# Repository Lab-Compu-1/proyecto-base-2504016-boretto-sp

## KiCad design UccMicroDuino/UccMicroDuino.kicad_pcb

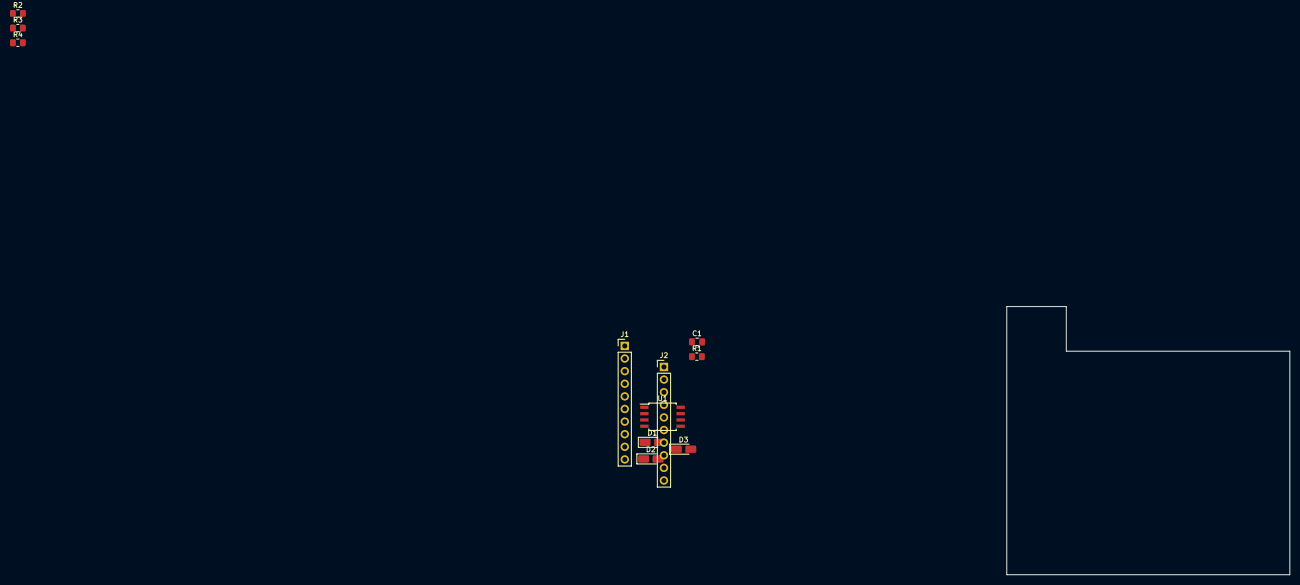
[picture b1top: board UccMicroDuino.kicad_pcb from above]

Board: 2 copper layers, 57.0 x 54.0 mm, 11 parts (0 on the bottom side), 9 nets, no tracks yet.

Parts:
C1: 0.1u; C_0805_2012Metric_Pad1.18x1.45mm_HandSolder
D1: PMLL4148L; D_MicroMELF_Handsoldering
D2, D3: 3.6V 1/2mW; D_MicroMELF_Handsoldering
J1, J2: Conn_01x10_Socket; PinHeader_1x10_P2.54mm_Vertical
R1: 1.5KΩ 5% 1/8W; R_0805_2012Metric_Pad1.20x1.40mm_HandSolder
R2: 68Ω 5% 1/8W; R_0805_2012Metric_Pad1.20x1.40mm_HandSolder
R3, R4: 330Ω 5% 1/8W; R_0805_2012Metric_Pad1.20x1.40mm_HandSolder
U1: ATtiny85-20S; SOIC-8W_5.3x5.3mm_P1.27mm

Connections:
+5V: C1.1, D1.1 (K), J2.1, R1.1, U1.8 (VCC)
GND: C1.2, D2.2 (A), D3.2 (A), J2.2, R3.2, R4.2, U1.4 (GND)
unnamed: D2.1 (K), R1.2, R2.2
unnamed: J2.5, U1.6 (PB1)
unnamed: J2.4, U1.5 (AREF/PB0)
unnamed: J2.6, U1.7 (PB2)
unnamed: J2.7, R2.1, U1.2 (XTAL1/PB3)
unnamed: J2.8, U1.3 (XTAL2/PB4)
unnamed: J2.9, U1.1 (~RESET/PB5)

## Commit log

2025-03-17 GitHub Classroom Feedback
2025-03-17 Setting up GitHub Classroom Feedback
